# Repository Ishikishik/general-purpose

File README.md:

# General Purpose
機械部品とPCB。プログラムを含むものはそれぞれのリポジトリをチェック

## 目次
- [Mechanical Parts](#mechanical-parts)
  - [LinearRail](#linearrail)
  - [Bearing](#bearing)
- [PCB](#pcb)
  - [esp32s3devboard](#esp32s3devboard)
  - [2.1DC](#21dc)

## Mechanical Parts
機械に使われる汎用部品集です。  
主に OpenSCAD 製で、パラメータを変更するだけで様々なサイズの部品を生成できます。

### LinearRail

リニアレールとスライダーブロックです。
寸法を変更することで用途に応じたサイズを生成できます。

### Bearing

いい感じのベアリングです。

## PCB
### esp32s3devboard

esp32s3のdevboardです。細長いのでブレボに刺すのにおすすめ

### 2.1DC 

2.1のdcを2.54ミリピッチに変えることができる。ラズパイにそのままブッさせる。

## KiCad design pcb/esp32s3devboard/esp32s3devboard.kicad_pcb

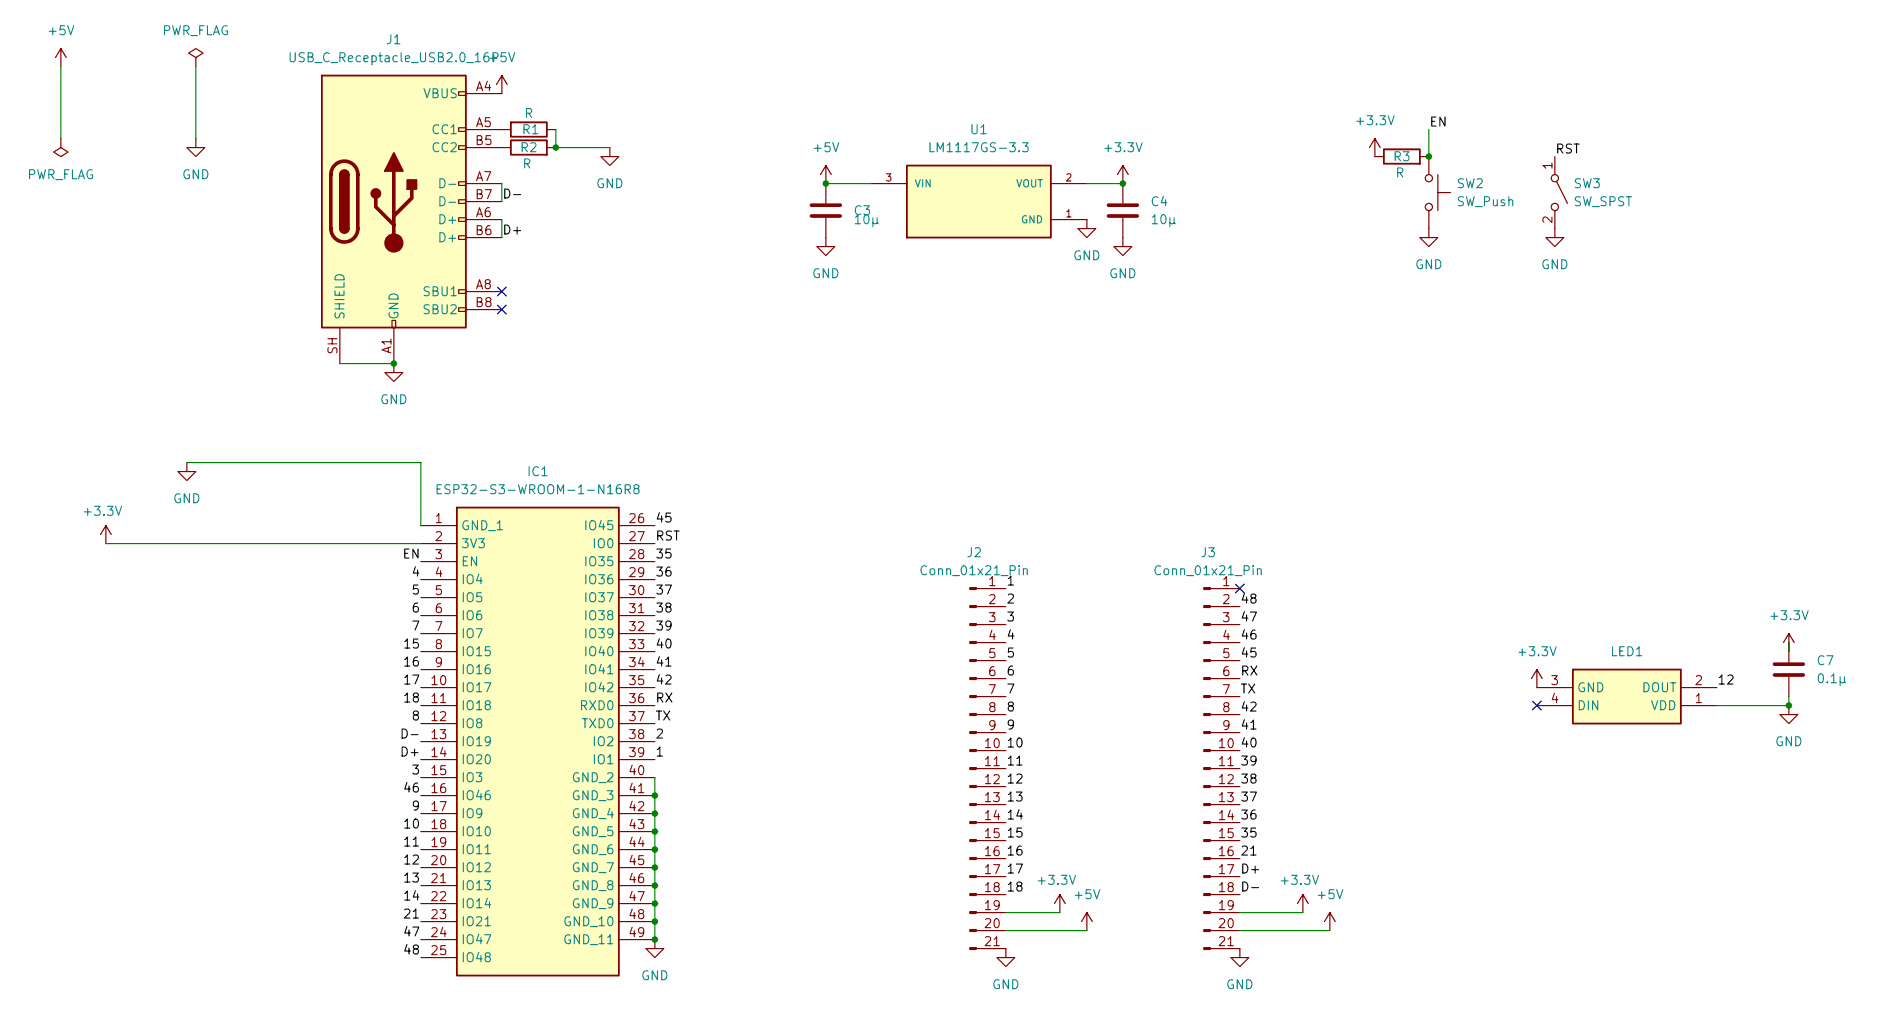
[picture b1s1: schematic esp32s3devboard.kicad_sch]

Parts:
C3, C4: 10μ; C_0603_1608Metric
C7: 0.1μ; C_0603_1608Metric
IC1: ESP32-S3-WROOM-1-N16R8; ESP32-S3-WROOM-1; Manufacturer_Part_Number ESP32-S3-WROOM-1-N16R8; Mouser Part Number 356-ESP32S3WRM1N16R8
J1: USB_C_Receptacle_USB2.0_16P; USB_C_Receptacle_GCT_USB4105-xx-A_16P_TopMnt_Horizontal
J2, J3: Conn_01x21_Pin; PinHeader_1x21_P2.54mm_Vertical
LED1: OSTW3535C1A; OTHER-4_3.48x3.48mm_P1.0mm; Manufacturer_Part_Number WS2812C-2020
R1, R2, R3: R; C_0402_1005Metric
SW2: SW_Push; LS6J2MT
SW3: SW_SPST; SSSS213202
U1: LM1117GS-3.3; SOT-223-3_TabPin2

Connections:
+3.3V: C4.1, C7.1, IC1.2 (3V3), J2.19, J3.19, LED1.3 (GND), R3.1, U1.2 (VOUT), U1.4 (VOUT); also elsewhere on the board
+5V: C3.1, J1.A4 (VBUS), J1.A9 (VBUS), J1.B4 (VBUS), J1.B9 (VBUS), J2.20, J3.20, U1.3 (VIN)
/1: IC1.39 (IO1), J2.1
/2: IC1.38 (IO2), J2.2
/3: IC1.15 (IO3), J2.3
/4: IC1.4 (IO4), J2.4
/5: IC1.5 (IO5), J2.5
/6: IC1.6 (IO6), J2.6
/7: IC1.7 (IO7), J2.7
/8: IC1.12 (IO8), J2.8
/9: IC1.17 (IO9), J2.9
/10: IC1.18 (IO10), J2.10
/11: IC1.19 (IO11), J2.11
/12: IC1.20 (IO12), J2.12, LED1.2 (DOUT)
/13: IC1.21 (IO13), J2.13
/14: IC1.22 (IO14), J2.14
/15: IC1.8 (IO15), J2.15
/16: IC1.9 (IO16), J2.16
/17: IC1.10 (IO17), J2.17
/18: IC1.11 (IO18), J2.18
/21: IC1.23 (IO21), J3.16
/35: IC1.28 (IO35), J3.15
/36: IC1.29 (IO36), J3.14
/37: IC1.30 (IO37), J3.13
/38: IC1.31 (IO38), J3.12
/39: IC1.32 (IO39), J3.11
/40: IC1.33 (IO40), J3.10
/41: IC1.34 (IO41), J3.9
/42: IC1.35 (IO42), J3.8
/45: IC1.26 (IO45), J3.5
/46: IC1.16 (IO46), J3.4
/47: IC1.24 (IO47), J3.3
/48: IC1.25 (IO48), J3.2
/D+: IC1.14 (IO20), J1.A6 (D+), J1.B6 (D+), J3.17
/D-: IC1.13 (IO19), J1.A7 (D-), J1.B7 (D-), J3.18
/EN: IC1.3 (EN), R3.2, SW2.1
/RST: IC1.27 (IO0), SW3.1 (A)
/RX: IC1.36 (RXD0), J3.6
/TX: IC1.37 (TXD0), J3.7
GND: C3.2, C4.2, C7.2, IC1.1 (GND_1), IC1.40 (GND_2), IC1.41 (GND_3), IC1.42 (GND_4), IC1.43 (GND_5), IC1.44 (GND_6), IC1.45 (GND_7), IC1.46 (GND_8), IC1.47 (GND_9), IC1.48 (GND_10), IC1.49 (GND_11), J1.A1 (GND), J1.A12 (GND), J1.B1 (GND), J1.B12 (GND), J1.SH (SHIELD), J2.21, J3.21, LED1.1 (VDD), R1.1, R2.2, SW2.2, SW3.2 (B), U1.1 (GND); also elsewhere on the board
unnamed: J1.A5 (CC1), R1.2
unnamed: J1.B5 (CC2), R2.1

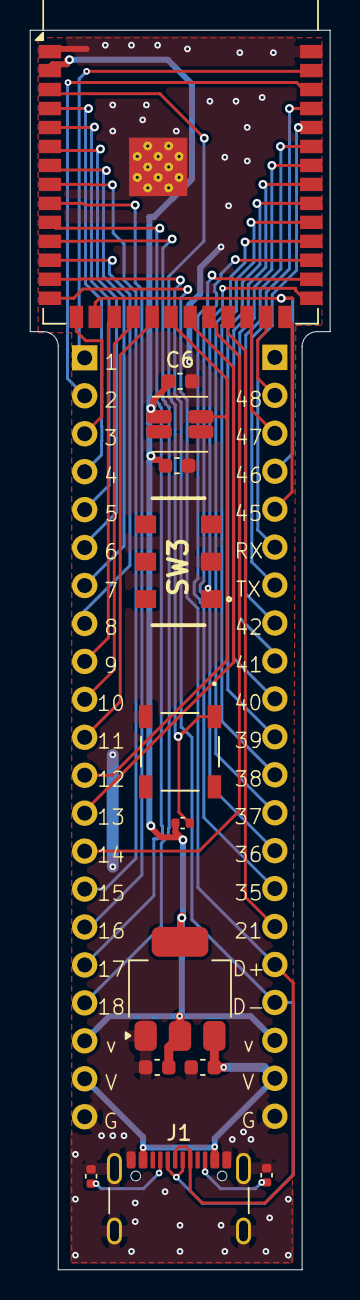
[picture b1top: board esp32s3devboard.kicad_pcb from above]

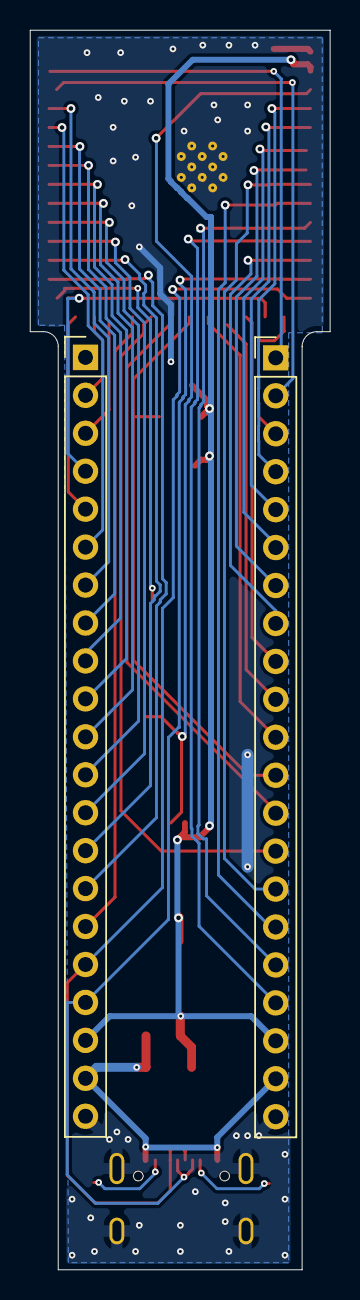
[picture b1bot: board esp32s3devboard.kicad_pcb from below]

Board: 2 copper layers, 20.1 x 83.0 mm, 15 parts (2 on the bottom side), 42 nets.

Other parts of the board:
C5, C6: C; C_0603_1608Metric

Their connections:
+3.3V: C5.1, C6.1; also elsewhere on the board
GND: C5.2, C6.2; also elsewhere on the board
